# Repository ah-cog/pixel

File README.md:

Pixel
=====

Pixel is a modular, tangible interface for physical computing.

## Physical Design ##

TinkerCad
https://tinkercad.com/dashboard/projects/bFf1tuIbj8z-pixel

Autodesk 123D Design
http://123dapp.com/Project/Pixel/1861964

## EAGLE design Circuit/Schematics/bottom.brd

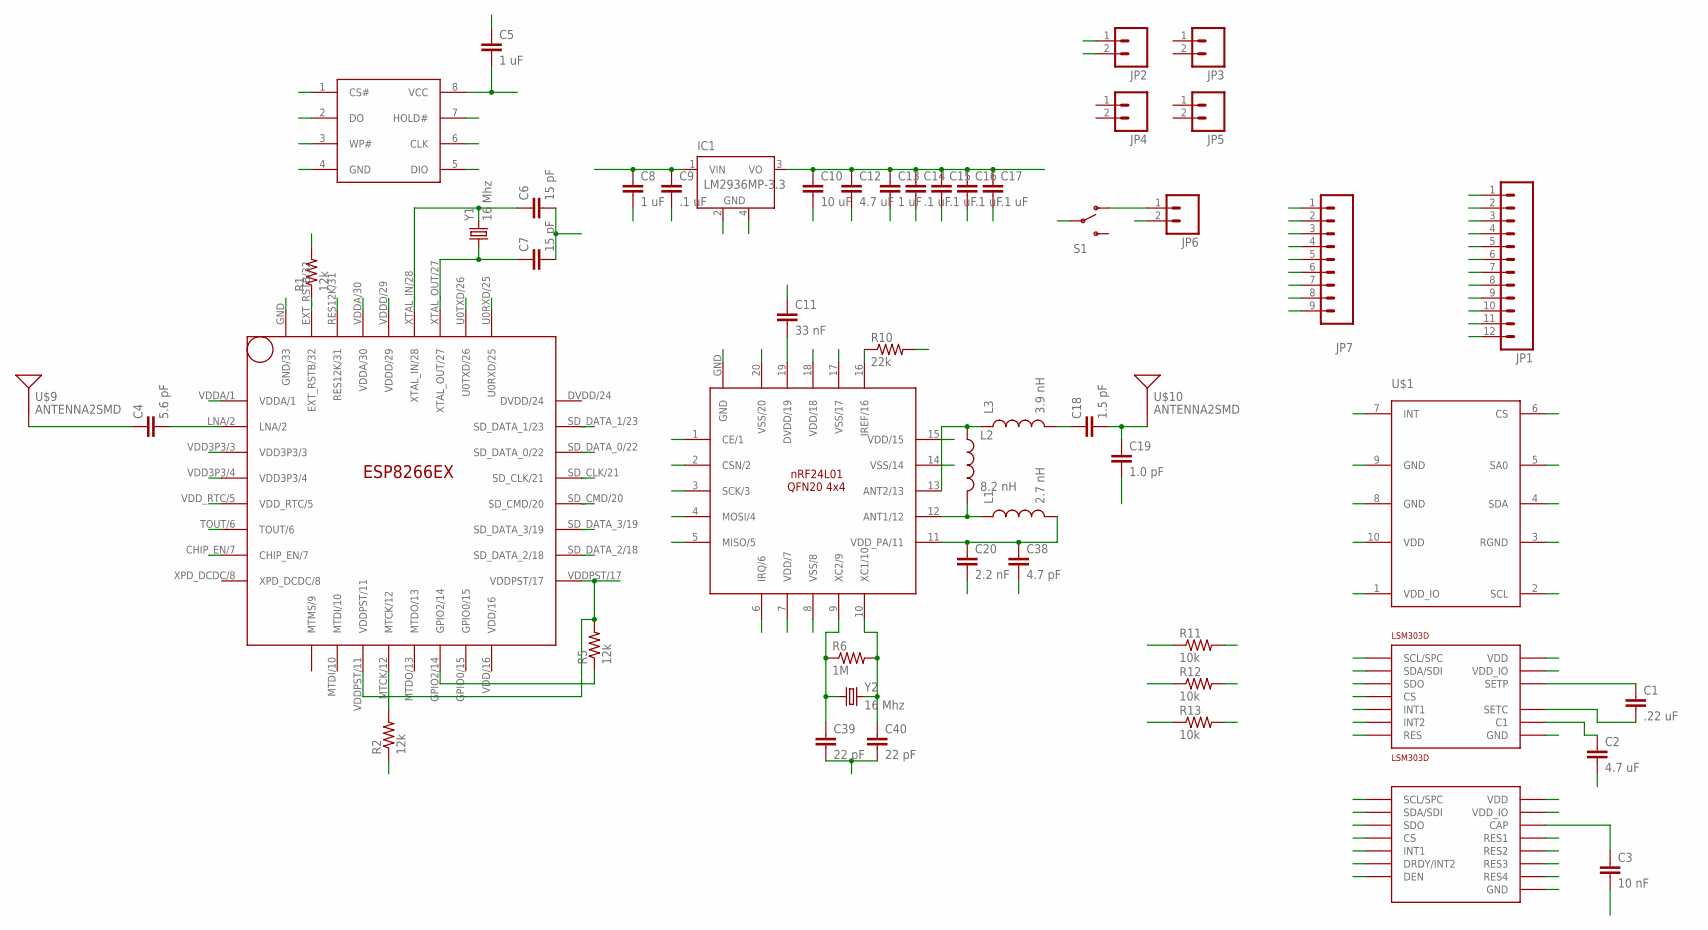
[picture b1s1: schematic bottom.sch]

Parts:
C1: .22 uF; 0603-CAP
C2, C12: 4.7 uF; 0603-CAP
C3: 10 nF; 0603-CAP
C4: 5.6 pF; 0603-CAP
C5, C8, C13: 1 uF; 0603-CAP
C6, C7: 15 pF; 0603-CAP
C9, C14, C15, C16, C17: .1 uF; 0603-CAP
C10: 10 uF; 0603-CAP
C11: 33 nF; 0603-CAP
C18: 1.5 pF; 0603-CAP
C19: 1.0 pF; 0603-CAP
C20: 2.2 nF; 0603-CAP
C38: 4.7 pF; 0603-CAP
C39, C40: 22 pF; 0603-CAP
IC1: LM2936MP-3.3; SOT223
JP1: M12PTH; 1X12
JP2, JP3, JP4, JP5, JP6: M02LOCK; 1X02_LOCK
JP7: M09; 1X09
L1: 2.7 nH; C0402
L2: 8.2 nH; C0402
L3: 3.9 nH; C0402
L3GD20H: L3GD20H; LGA16L
LSM303D: LSM303D; LGA16L
MESH: NRF24L01; QFN20(4X4)
R1, R2, R5: 12k; 0603-RES
R6: 1M; 0603-RES
R10: 22k; 0603-RES
R11, R12, R13: 10k; 0603-RES
S1: SWITCH-SPDT-SMD-A; SWITCH-SPST-SMD-A
U$1: LPS25H
U$9, U$10: ANTENNA2SMD; ANTENNA-CHIP2
WIFI: ESP8266EX; QFN32
WIFI_STORAGE: 25Q40; SOP8
Y1, Y2: 16 Mhz; CRYSTAL-SMD-5X3

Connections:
CE: JP7.3, MESH.1 (CE/1)
CSN: JP7.4, MESH.2 (CSN/2)
GND: C2.2, C3.2, C5.1, C6.2, C7.2, C8.2, C9.2, C10.2, C11.1, C12.2, C13.2, C14.2, C15.2, C16.2, C17.2, C19.2, C20.2, C38.2, C39.2, C40.2, IC1.2 (GND), IC1.4 (GND), JP1.1, JP1.2, JP1.3, JP1.4, JP1.5, JP1.6, JP2.2, JP6.2, L3GD20H.P$8 (DEN), L3GD20H.P$9 (RES1), L3GD20H.P$10 (RES2), L3GD20H.P$11 (RES3), L3GD20H.P$12 (GND), L3GD20H.P$13 (GND), LSM303D.P$5 (GND), LSM303D.P$10 (RES), LSM303D.P$12 (GND), LSM303D.P$13 (GND), LSM303D.P$16 (GND), MESH.8 (VSS/8), MESH.14 (VSS/14), MESH.17 (VSS/17), MESH.20 (VSS/20), R1.2, R2.1, R10.2, U$1.3 (RGND), U$1.8 (GND), U$1.9 (GND), WIFI.GND (GND/33), WIFI_STORAGE.4 (GND)
IQR: MESH.6 (IRQ/6)
MISO: JP7.6, MESH.5 (MISO/5)
MOSI: JP7.5, MESH.4 (MOSI/4)
unnamed: C4.1, U$9.FEED
unnamed: R5.1, WIFI.GPIO2/14
unnamed: R2.2, WIFI.MTCK/12
unnamed: L1.1, L2.2, MESH.12 (ANT1/12)
unnamed: C18.1, L3.2
unnamed: C18.2, C19.1, U$10.FEED
unnamed: C4.2, WIFI.LNA/2
unnamed: C39.1, MESH.9 (XC2/9), R6.1, Y2.1
unnamed: C40.1, MESH.10 (XC1/10), R6.2, Y2.3 (2)
unnamed: C20.1, C38.1, L1.2, MESH.11 (VDD_PA/11)
unnamed: L2.1, L3.1, MESH.13 (ANT2/13)
unnamed: MESH.16 (IREF/16), R10.1
unnamed: C11.2, MESH.19 (DVDD/19)
unnamed: C1.2, LSM303D.P$2 (SETC)
unnamed: C2.1, LSM303D.P$15 (C1)
unnamed: C3.1, L3GD20H.P$14 (CAP)
RST: R1.1, WIFI.EXT_RSTB/32
RTC: WIFI.VDD_RTC/5
RX_W: JP7.1, WIFI.U0TXD/26
SCK: JP7.7, MESH.3 (SCK/3)
SCL: JP7.9, L3GD20H.P$2 (SCL/SPC), LSM303D.P$4 (SCL/SPC), R12.2, U$1.2 (SCL)
SD-CLK: WIFI.SD_CLK/21, WIFI_STORAGE.6 (CLK)
SD-CMD: WIFI.SD_CMD/20, WIFI_STORAGE.1 (CS#)
SD-D0: WIFI.SD_DATA_0/22, WIFI_STORAGE.2 (DO)
SD-D1: WIFI.SD_DATA_1/23, WIFI_STORAGE.5 (DIO)
SD-D2: WIFI.SD_DATA_2/18, WIFI_STORAGE.7 (HOLD#)
SD-D3: WIFI.SD_DATA_3/19, WIFI_STORAGE.3 (WP#)
SDA: JP7.8, L3GD20H.P$3 (SDA/SDI), LSM303D.P$6 (SDA/SDI), R11.2, U$1.4 (SDA)
SDO: L3GD20H.P$4 (SDO), LSM303D.P$7 (SDO), R13.2, U$1.5 (SA0)
SETP: C1.1, LSM303D.P$3 (SETP)
TOUT: WIFI.TOUT/6
TX_W: JP7.2, WIFI.U0RXD/25
VIN: JP6.1, S1.1 (O)
VRAW: C8.1, C9.1, IC1.1 (VIN), S1.2
XTAL_IN: C6.1, WIFI.XTAL_IN/28, Y1.3 (2)
XTAL_OUT: C7.1, WIFI.XTAL_OUT/27, Y1.1

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
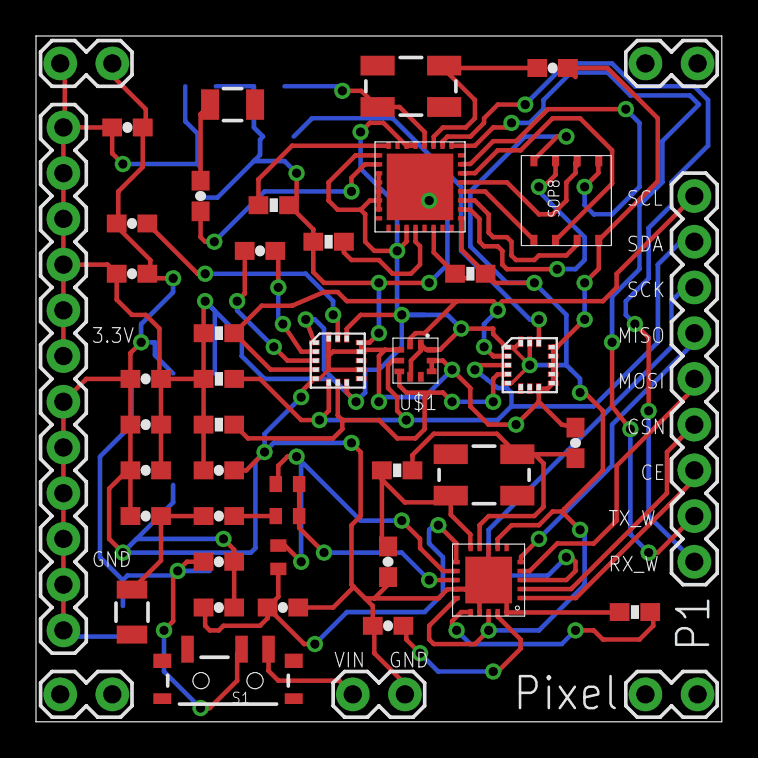
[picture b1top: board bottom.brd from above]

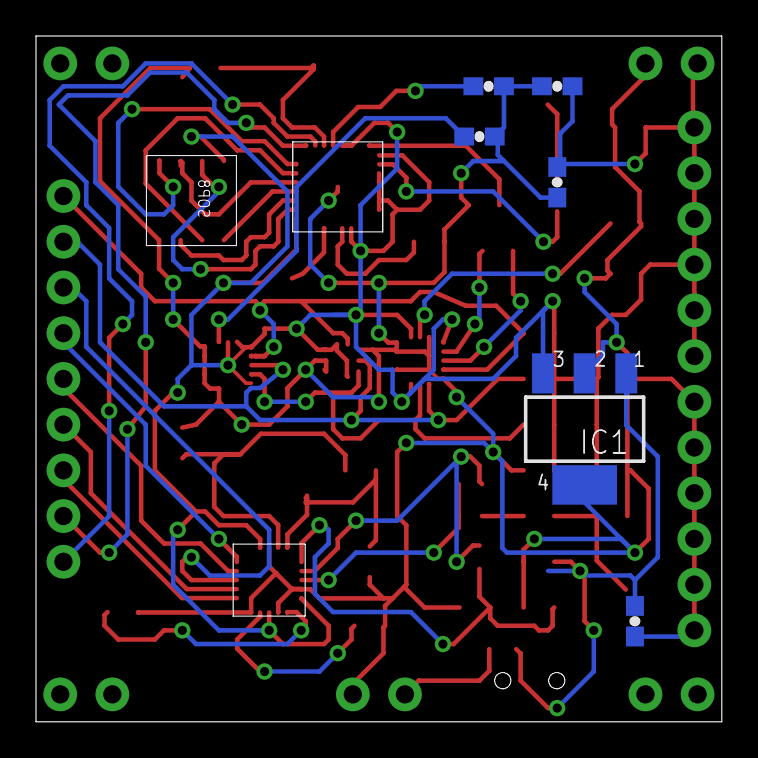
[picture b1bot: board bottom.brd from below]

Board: 2 copper layers, 38.1 x 38.1 mm, 53 parts (6 on the bottom side), 40 nets.

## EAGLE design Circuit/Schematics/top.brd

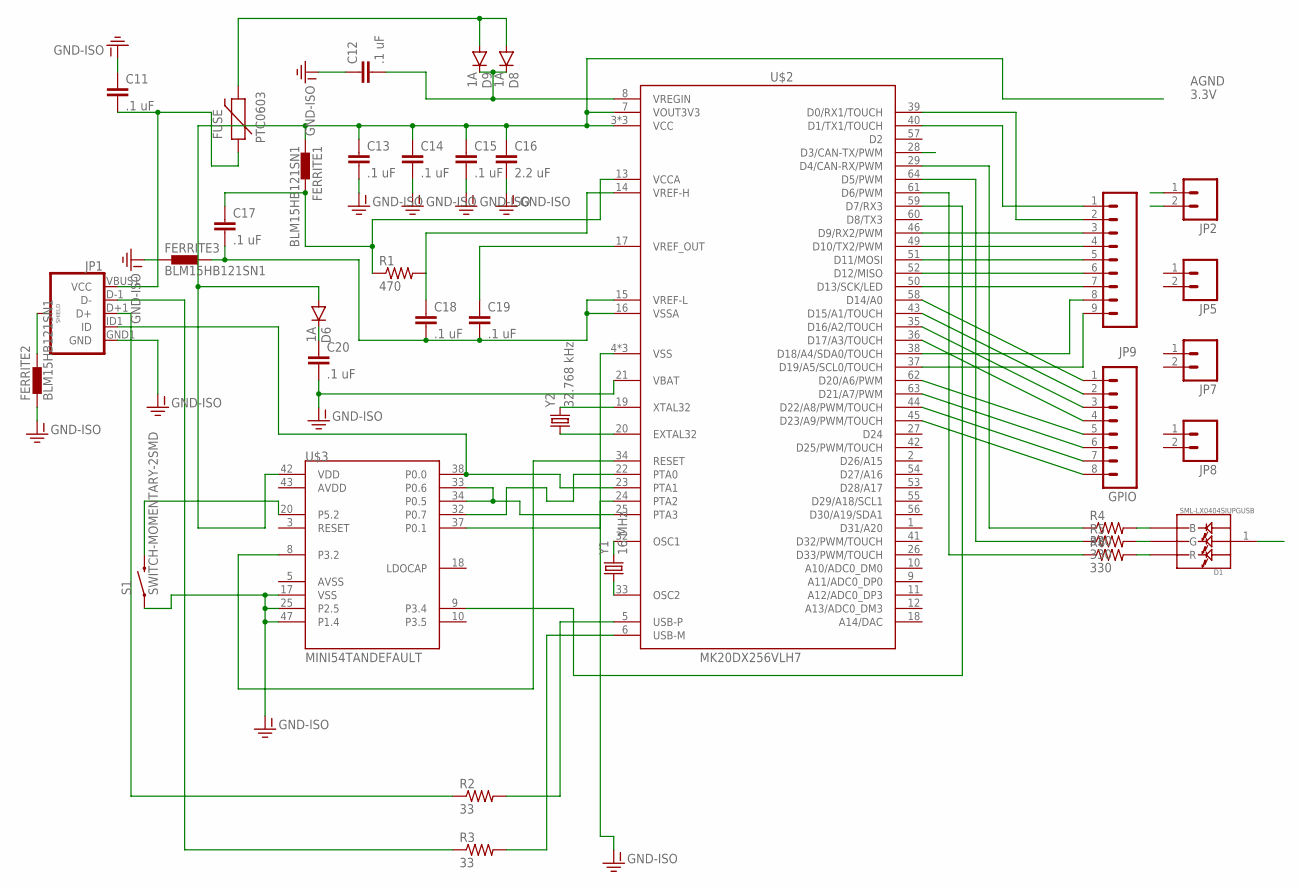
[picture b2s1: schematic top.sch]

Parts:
C11, C12, C13, C14, C15, C17, C18, C19, C20: .1 uF; 0603-CAP
C16: 2.2 uF; 0603-CAP
D1: SML-LX0404SIUPGUSB; 1MM_SQ_4PAD
D6, D8, D9: 1A; SOD-323
FERRITE1, FERRITE2, FERRITE3: BLM15HB121SN1; 0402
FUSE: PTC0603; 0603
GPIO: M08SILK_FEMALE_PTH; 1X08
JP1: USB_MICROB_PLUGCONN-11752; USB-B-MICRO-SMD_V03
JP2, JP5, JP7, JP8: M02LOCK; 1X02_LOCK
JP9: M09; 1X09
R1: 470; 0603-RES
R2, R3: 33; 0603-RES
R4, R5, R6: 330; 0603-RES
S1: SWITCH-MOMENTARY-2SMD; TACTILE-SWITCH-SMD
U$2: MK20DX256VLH7; QFP50P1200X1200X160-64N
U$3: MINI54TANDEFAULT; QFP50P900X900X160-48N
Y1: 16 MHz; CRYSTAL-SMD-5X3
Y2: 32.768 kHz; CRYSTAL-SMD-5X3

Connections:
3.3V: C13.1, C14.1, C15.1, C16.1, D1.1 (VDD), D6.A, FERRITE1.1, JP2.1, U$2.3 (VCC), U$2.7 (VOUT3V3), U$2.30 (VCC), U$2.48 (VCC), U$3.42 (VDD)
AGND: C17.2, C18.2, C19.2, FERRITE3.2, U$2.15 (VREF-L), U$2.16 (VSSA)
CE: JP9.3, U$2.46 (D9/RX2/PWM)
GND-ISO: C11.1, C12.1, C13.2, C14.2, C15.2, C16.2, C20.2, FERRITE2.1, FERRITE3.1, JP1.GND1 (GND), JP2.2, S1.1, U$2.4 (VSS), U$2.21 (VBAT), U$2.31 (VSS), U$2.47 (VSS), U$3.17 (VSS), U$3.25 (P2.5), U$3.47 (P1.4)
unnamed: C19.1, U$2.17 (VREF_OUT)
unnamed: C12.2, D8.C, D9.C, U$2.8 (VREGIN)
unnamed: C17.1, FERRITE1.2, R1.1, U$2.13 (VCCA)
unnamed: C18.1, R1.2
unnamed: FERRITE2.2, JP1.SHIELD1 (SHIELD), JP1.SHIELD2 (SHIELD), JP1.SHIELD3 (SHIELD)
unnamed: S1.3 (2), U$3.20 (P5.2)
unnamed: C20.1, D6.C
unnamed: JP1.D+1 (D+), R2.1
unnamed: U$2.34 (RESET), U$3.8 (P3.2)
unnamed: JP1.ID1 (ID), U$2.23 (PTA1), U$3.38 (P0.0)
unnamed: U$2.25 (PTA3), U$3.33 (P0.6), U$3.34 (P0.5)
unnamed: U$2.22 (PTA0), U$3.32 (P0.7)
unnamed: U$2.24 (PTA2), U$3.37 (P0.1)
unnamed: U$2.59 (D7/RX3), U$3.9 (P3.4)
unnamed: JP1.D-1 (D-), R3.1
unnamed: R2.2, U$2.5 (USB-P)
unnamed: R3.2, U$2.6 (USB-M)
unnamed: JP9.4, U$2.49 (D10/TX2/PWM)
unnamed: U$2.19 (XTAL32), Y2.3 (2)
unnamed: U$2.20 (EXTAL32), Y2.1
unnamed: U$2.32 (OSC1), Y1.3 (2)
unnamed: U$2.33 (OSC2), Y1.1
unnamed: JP9.5, U$2.51 (D11/MOSI)
unnamed: JP9.6, U$2.52 (D12/MISO)
unnamed: GPIO.1, U$2.58 (D14/A0)
unnamed: GPIO.2, U$2.43 (D15/A1/TOUCH)
unnamed: GPIO.3, U$2.35 (D16/A2/TOUCH)
unnamed: D1.3 (B), R4.2
unnamed: D1.4 (G), R5.2
unnamed: D1.2 (R), R6.2
unnamed: GPIO.4, U$2.36 (D17/A3/TOUCH)
unnamed: GPIO.5, U$2.62 (D20/A6/PWM)
unnamed: GPIO.6, U$2.63 (D21/A7/PWM)
unnamed: GPIO.7, U$2.44 (D22/A8/PWM/TOUCH)
unnamed: GPIO.8, U$2.45 (D23/A9/PWM/TOUCH)
unnamed: R5.1, U$2.64 (D5/PWM)
unnamed: R4.1, U$2.29 (D4/CAN-RX/PWM)
unnamed: C11.2, FUSE.1, JP1.VBUS1 (VCC)
unnamed: R6.1, U$2.61 (D6/PWM)
SCK: JP9.7, U$2.50 (D13/SCK/LED)
SCL_T: JP9.9, U$2.37 (D19/A5/SCL0/TOUCH)
SDA_T: JP9.8, U$2.38 (D18/A4/SDA0/TOUCH)
T_RX: JP9.2, U$2.39 (D0/RX1/TOUCH)
T_TX: JP9.1, U$2.40 (D1/TX1/TOUCH)
VIN: D8.A, D9.A, FUSE.2

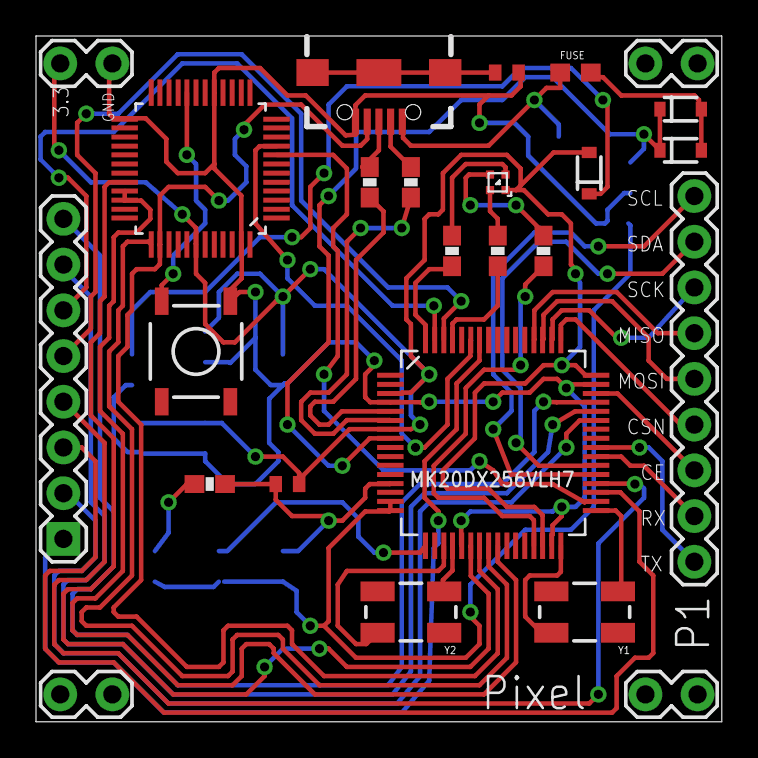
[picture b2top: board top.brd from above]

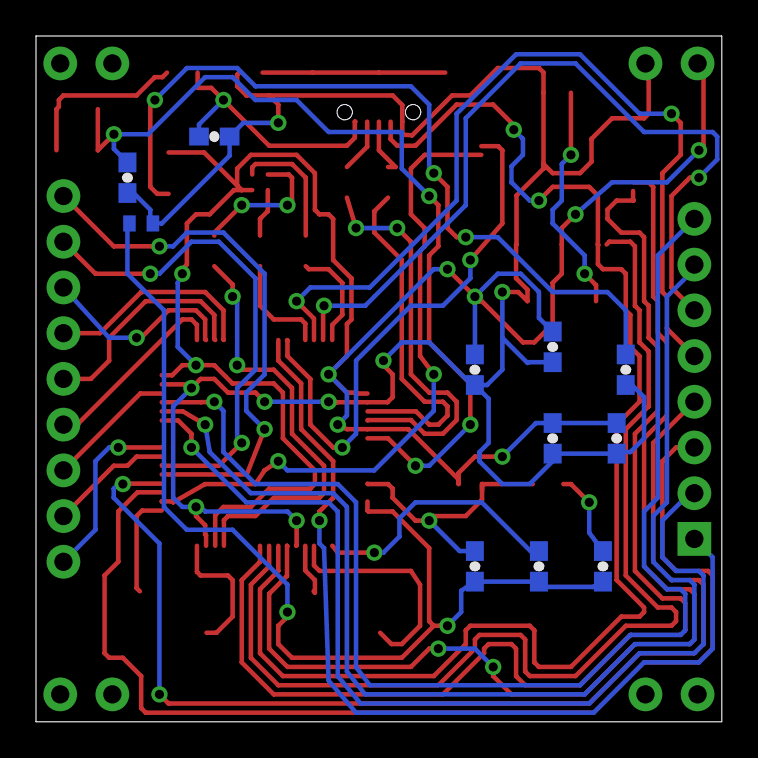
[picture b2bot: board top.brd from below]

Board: 2 copper layers, 38.1 x 38.1 mm, 36 parts (11 on the bottom side), 49 nets.

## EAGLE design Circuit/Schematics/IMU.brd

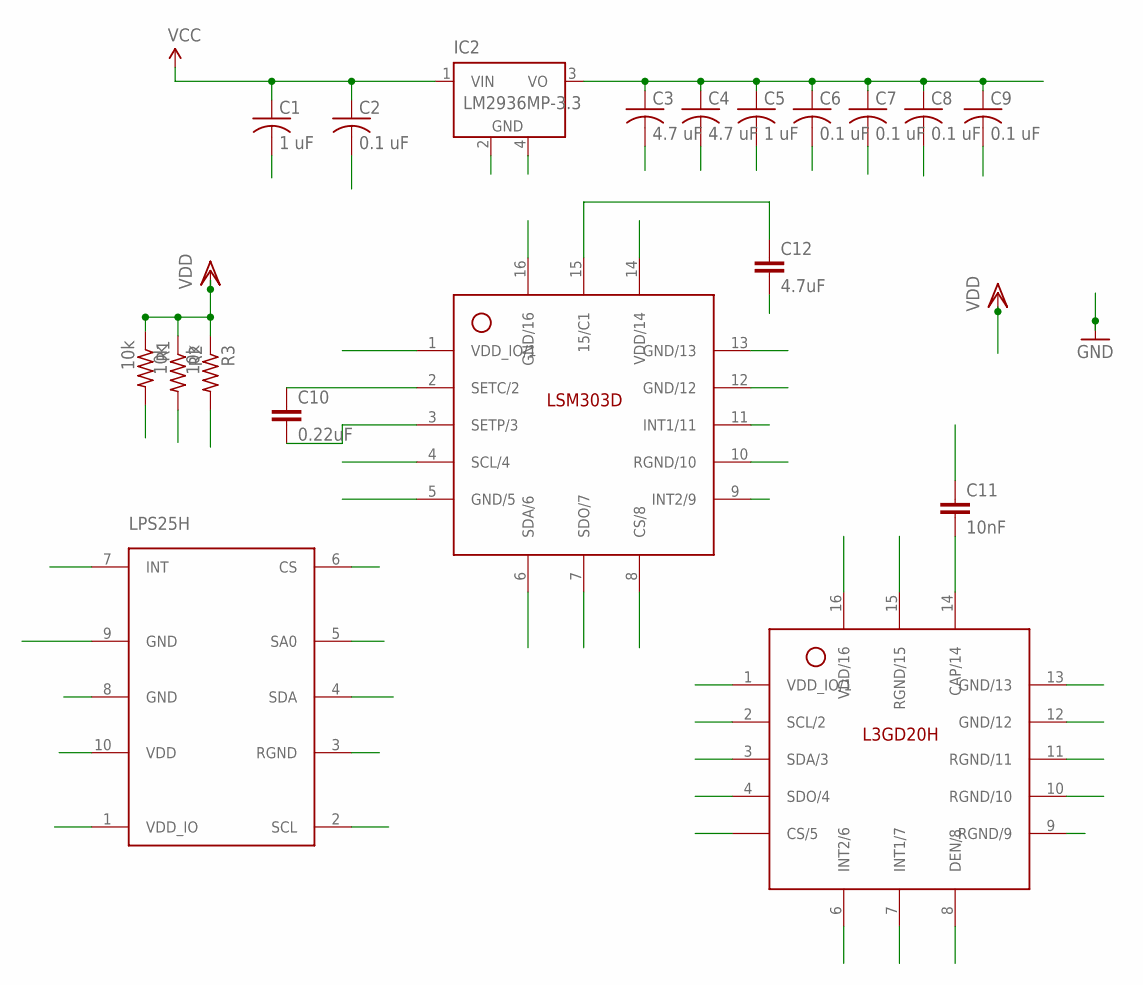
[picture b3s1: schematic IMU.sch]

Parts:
C1, C5: 1 uF; C0805
C2, C6, C7, C8, C9: 0.1 uF; C0805
C3, C4: 4.7 uF; C0805
C10: 0.22uF; 0603-CAP
C11: 10nF; 0603-CAP
C12: 4.7uF; 0603-CAP
IC2: LM2936MP-3.3; SOT223
LPS25H: LPS25H
R1, R2, R3: 10k; R0805
U$1: L3GD20H; LGA-16
U$2: LSM303D; LGA-16

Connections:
GND: C1.2, C2.2, C3.2, C4.2, C5.2, C6.2, C7.2, C8.2, C9.2, C11.1, C12.2, IC2.2 (GND), IC2.4 (GND), LPS25H.8 (GND), LPS25H.9 (GND), U$1.8 (DEN/8), U$1.9 (RGND/9), U$1.10 (RGND/10), U$1.11 (RGND/11), U$1.12 (GND/12), U$1.13 (GND/13), U$1.16 (VDD/16), U$2.5 (GND/5), U$2.10 (RGND/10), U$2.12 (GND/12), U$2.13 (GND/13), U$2.16 (GND/16)
unnamed: C10.1, U$2.2 (SETC/2)
unnamed: C10.2, U$2.3 (SETP/3)
unnamed: C12.1, U$2.15 (15/C1)
unnamed: C11.2, U$1.14 (CAP/14)
SCL: LPS25H.2 (SCL), R2.2, U$1.2 (SCL/2), U$2.4 (SCL/4)
SDA: LPS25H.4 (SDA), R1.2, U$1.3 (SDA/3), U$2.6 (SDA/6)
SDO: LPS25H.5 (SA0), R3.2, U$1.4 (SDO/4), U$2.7 (SDO/7)
VCC: C1.1, C2.1, IC2.1 (VIN)
VDD: C3.1, C4.1, C5.1, C6.1, C7.1, C8.1, C9.1, IC2.3 (VO), LPS25H.1 (VDD_IO), LPS25H.6 (CS), LPS25H.10 (VDD), R1.1, R2.1, R3.1, U$1.1 (VDD_IO/1), U$1.5 (CS/5), U$1.15 (RGND/15), U$2.1 (VDD_IO/1), U$2.8 (CS/8), U$2.14 (VDD/14)

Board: 2 copper layers, 19 parts (0 on the bottom side), 10 nets, no tracks yet.

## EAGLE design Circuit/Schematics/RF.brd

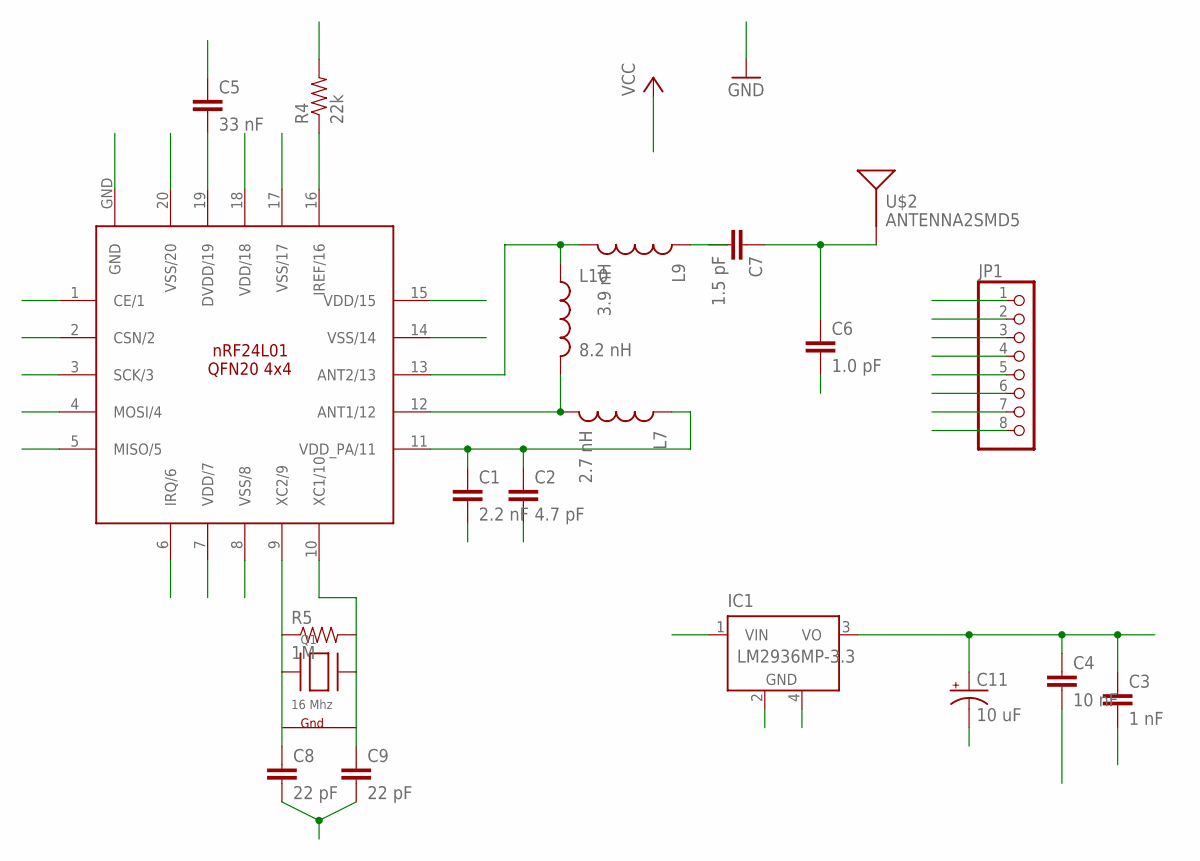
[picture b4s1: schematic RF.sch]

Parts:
C1: 2.2 nF; 0805
C2: 4.7 pF; 0805
C3: 1 nF; 0805
C4: 10 nF; 0805
C5: 33 nF; 0805
C6: 1.0 pF; 0805
C7: 1.5 pF; 0805
C8, C9: 22 pF; 0805
C11: 10 uF; EIA3216
IC1: LM2936MP-3.3; SOT223
JP1: PINHD-1X8BIG; 1X08-BIG
L7: 2.7 nH; C0402
L9: 3.9 nH; C0402
L10: 8.2 nH; C0402
Q1: 16 Mhz; NX3225
R4: 22k; 0805
R5: 1M; 0805
U$1: NRF24L01; QFN20(4X4)
U$2: ANTENNA2SMD5; ANTENNA-CHIP5

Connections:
ANT: C6.1, C7.1, U$2.FEED
CE: JP1.2, U$1.1 (CE/1)
CSN: JP1.3, U$1.2 (CSN/2)
G1: Q1.4 (G1)
G2: Q1.2 (G2)
GND: C1.2, C2.2, C3.2, C4.2, C5.1, C6.2, C8.2, C9.2, C11.C (-), IC1.2 (GND), IC1.4 (GND), JP1.8, R4.2, U$1.8 (VSS/8), U$1.14 (VSS/14), U$1.17 (VSS/17), U$1.20 (VSS/20), U$1.GND
IQR: JP1.7, U$1.6 (IRQ/6)
MISO: JP1.6, U$1.5 (MISO/5)
MOSI: JP1.5, U$1.4 (MOSI/4)
unnamed: C8.1, Q1.1 (X1), R5.1, U$1.9 (XC2/9)
unnamed: C9.1, Q1.3 (X2), R5.2, U$1.10 (XC1/10)
unnamed: C1.1, C2.1, L7.1, U$1.11 (VDD_PA/11)
unnamed: L7.2, L10.2, U$1.12 (ANT1/12)
unnamed: L9.2, L10.1, U$1.13 (ANT2/13)
unnamed: C7.2, L9.1
unnamed: R4.1, U$1.16 (IREF/16)
unnamed: C5.2, U$1.19 (DVDD/19)
SCK: JP1.4, U$1.3 (SCK/3)
VCC: IC1.1 (VIN)
VDD: C3.1, C4.1, C11.A (+), IC1.3 (VO), JP1.1, U$1.7 (VDD/7), U$1.15 (VDD/15), U$1.18 (VDD/18)

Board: 2 copper layers, 20 parts (0 on the bottom side), 17 nets, no tracks yet.

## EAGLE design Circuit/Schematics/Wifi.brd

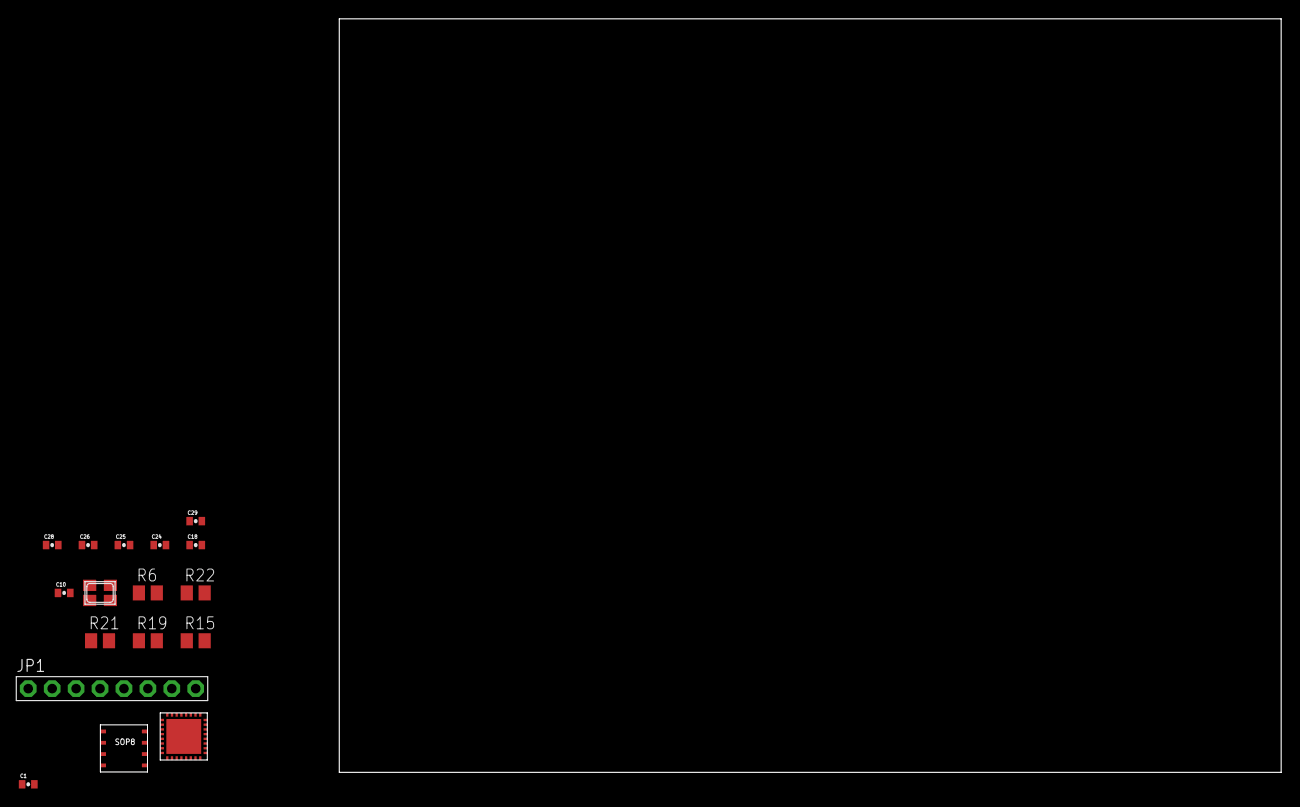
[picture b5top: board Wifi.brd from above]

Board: 2 copper layers, 125.3 x 79.9 mm, 17 parts (0 on the bottom side), 23 nets, no tracks yet.

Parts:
C1: 5.6 pF; 0402-CAP
C10, C24: 15 pF; 0402-CAP
C18: 1 uF; 0402-CAP
C25, C26, C29: 100 nF; 0402-CAP
C28: 10 uF; 0402-CAP
JP1: 1X08-BIG
Q1: NX3225
R6, R15, R19, R21: M0805
R22: 12k; M0805
U$1: ESP8266EX; QFN32
U$2: 25Q40; SOP8

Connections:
CHIP_EN: JP1.6, R21.2, U$1.CHIP_EN/7
CLK: U$1.SD_CLK/21, U$2.6
CS: U$1.SD_CMD/20, U$2.1
GND: C10.1, C18.1, C24.1, JP1.1, R15.2, R22.2, U$1.GND, U$2.4
unnamed: R22.1, U$1.RES12K/31
unnamed: C24.2, Q1.3, U$1.XTAL_IN/28
unnamed: C25.2, C26.2, C28.2, C29.2
unnamed: C10.2, Q1.1, U$1.XTAL_OUT/27
unnamed: R6.2, U$1.VDDPST/11, U$1.VDDPST/17
unnamed: R19.2, U$1.GPIO0/15
unnamed: R6.1, U$1.GPIO2/14
unnamed: R15.1, U$1.MTDO/13
unnamed: C1.1, U$1.LNA/2
RST: JP1.5, U$1.EXT_RSTB/32
RTC: JP1.8, U$1.VDD_RTC/5
RXD: JP1.3, U$1.U0RXD/25
SD0: U$1.SD_DATA_0/22, U$2.2
SD1: U$1.SD_DATA_1/23, U$2.5
SD2: U$1.SD_DATA_2/18, U$2.7
SD3: U$1.SD_DATA_3/19, U$2.3
TOUT: JP1.7, U$1.TOUT/6
TXD: JP1.4, U$1.U0TXD/26
VCC: C18.2, C25.1, C26.1, C28.1, C29.1, JP1.2, R19.1, R21.1, U$1.VDD3P3/3, U$1.VDD3P3/4, U$1.VDDA/1, U$1.VDDA/30, U$1.VDDD/29, U$2.8

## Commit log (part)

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2013-07-23 Initial commit.
2013-07-23 Added basic iterator to Arduino module code and Processing visualizer.
2013-10-05 HackMIT, Day 1 (Saturday). Got basic RadioBlock communication working between two Arduinos and RadioBlocks.
    Using Arduino Unos, each set up with a RadioBlock. The Arduino Uno with
    the RadioBlock with orange sticker labeled "0" is set with the address
    0x1000 (using the RadioBlockSerialInterface::setAddress() function).
    The other Arduino, labeled "1" is set with address 0x1001.
2013-10-05 HackMIT, Day 1 (Saturday). Code successfully communicates state of Switch 1 (SWT-GND1) on 2x2 button module.
2013-10-06 HackMIT, Day 1 (Saturday). Added initial button module LED control and I/O code.
2013-10-06 HackMIT, Day 2 (Sunday). Set sound for each row.
2013-10-06 HackMIT, Day 2 (Sunday). Added function to get button input and set button state.
2013-10-06 HackMIT, Day 2 (Sunday). Implemented column-by-column baseline iterator. Updated toggle behavior, particularly how lights are enabled.
2013-10-06 HackMIT, Day 2 (Sunday). Implemented simple sound playback on column activation.
2013-10-06 HackMIT, Day 2 (Sunday). Added basic state synchronization.
2013-10-12 HackRU, Day 1 (Saturday). Initial code. Basically same form HackMIT, but primed to change a lot in the next 20 hours.
2013-10-13 HackRU, Day 2 (Sunday). Added relay and accelerometer template sketches.
2013-10-13 HackRU, Day 2 (Sunday). Integrated accelerometer code into main node sketch.
2013-10-13 HackRU, Day 2 (Sunday). Added basic RadioBlocks code (untest).
2013-10-13 HackRU, Day 2 (Sunday). RadioBlocks verified to work. Next up, communicate meaningful information bi-directionally.
2013-10-13 HackRU, Day 2 (Sunday). Near-final code. Right now, nodes communicate, but don't affect each other.
2013-10-13 HackRU, Day 2 (Sunday). Final (?) demo code.
2013-11-03 Moved ModuleV1 and HUD code made while residing at the Tinkering Studio at The Exploratorium into a folder named Tinkering Studio.
2013-11-03 Added Arduino code for MinIMU-10 IMU for orientation sensing.
2013-11-03 (Once again…) Corrected naming problem in previous commit.
2013-11-04 Added AltIMU-10 support STL file.
2013-11-04 Fixed bug in Gesture Visualizer Deux. Added physical prototypes CAD files.
2013-11-11 Added CADf files for TinyDuino stack support.
2013-11-11 Updated TinyDuino stack support CAD file.
2013-11-11 Updated WiFi module support CAD file.
2013-11-11 Updated CAD file for TinyDuino Stack Support.
2013-11-11 Updated TinyDuino support CAD file.
2013-11-11 Cleaned up CC3000 web server code.
2013-11-12 Updated RadioBlocks and TinyDuino CAD files.
2013-11-22 Added new sketch that seems to integrate SD card reading and the WiFi module successfully. It's rather huge, though :-(.
2013-11-26 Added code templates. Added initial IMU data for creating gesture recognition heuristics.
2013-12-01 Added RadioBlocks example code.
2013-12-01 Added RadioBlocks Transmitter Demo for Arduino.
2013-12-02 Updated firmware with hard-coded (hack) code get device address and construct a list of neighbor addresses.
2013-12-02 Updated firmware. Added basic light control.
2013-12-15 Cleaned up firmware code.
2013-12-15 Updated firmware. Refactored firmware code.
2013-12-16 Updated firmware. Refactored, cleaned up.
2013-12-16 Updated firmware. Performs "ping pong".
2013-12-18 Updated firmware.
2013-12-24 Updated firmware. Added basic random pseudo-random number generator.
2013-12-26 Added data and data logger.
2013-12-26 Updated Visualizer. Added accelerometer and gyroscope data. Added basic plots.
2013-12-27 Created Gesture Data Plotter, a tool for helping construct gestural models from data.
2013-12-28 Added basic web-based creative interface.
2013-12-29 Added Looper. Replaced "Web Interface" with "Looper".
2013-12-29 Cleaned up Looper code.
2013-12-29 Updated Looper. Fixed big from last commit.
2014-01-01 Updated Looper. Added method to return event loop event seqeuence.
2014-01-01 Updated Looper. Added basic script renaming functionality.
2014-01-13 Update Gesture Data Plotter.
2014-01-31 (Work in progress.) Updated Looper with skeleton for dynamically adding multiple devices.
2014-02-02 Implemented basic multi-device interface. Time to clean up.
2014-02-02 Cleaned up.
2014-02-03 Cleanup and tweaks.
2014-02-03 Added "going" state variable to each event loop and ability to start and stop.
2014-02-03 Added Firepad.
2014-02-08 Updated Plotter.
2014-02-08 Updated Gesture Plotter. Got classification working pretty well for most gestures, almost always.
2014-02-08 Updated Gesture Plotter. Real-time gesture recognition demo. Hints that approach is okay, but needs tweaking.
2014-02-09 Renamed "Gesture Data Plotter" to "Gesture Plotter".
2014-02-09 Renamed "Gesture Visualizer Deux" to "Gesture Visualizer".
2014-02-09 Temporarily renamed "looper" to "Looper Behavior Sequencer".
2014-02-09 Updated Looper. Added basic behavior palette.
2014-02-09 Updated Looper. Added labels to behavior events.
2014-02-09 Updated Looper. Added behavior scripts to events in the event loop. The events execute the scripts to perform the behavior.
2014-02-09 Updated Looper. Added JavaScript code formatter.
2014-02-09 Updated Looper. Fixed behavior script ordering bug.
2014-02-15 Updated Gesture Visualizer and Looper.
2014-02-16 Updated Gesture Plotter. Cleaned up code.
2014-02-16 Updated Gesture Plotter and Data Transducer. Coded generator for Arduino gesture signatures.
2014-02-16 Updated IMU Data Transducer. Integrated gesture recognition code into Arduino code.
2014-02-24 Many updates and cleanup changes.
2014-03-04 Updated firmware. Added gesture sustain duration (how long the gesture is active, at minimum).
2014-03-04 Updated Gesture Plotter. Added gesture signature boundary visualization.
2014-03-05 Updated Gesture Plotter. Fixed a few bugs. Demoable.
2014-03-25 Updated Firmware. Moved gesture recognition code to separate header file.
2014-03-25 Renamed Gesture Plotter to Gesture Builder.
2014-03-26 Updated Gesture Builder. Fixed gesture matching window bug.
2014-03-27 Updated Looper Firmware.
2014-03-27 Updated Firmware. Demoable. Tested communication to be functional.
2014-03-29 Updated Firmware. Moved LED control code to Light.h.
2014-03-29 Updated Firmware. Moved gesture recognition code to Gesture.h.
    Gesture.h shouldn’t be confused with Gestures.h. Gestures.h contains
    only gesture models, generated by the Gesture Builder tool and doesn’t
    currently include functions for gesture recognition, too.
2014-03-29 Updated Firmware. Added RGB LED color gradual crossfade algorithm.
2014-03-29 Updated Firmware. Added incoming mesh message queue.
2014-03-30 Updated Firmware. Added function to return a Message structure for incoming messages (with source and message).
2014-03-30 Updated Firmware and Gesture Builder.
    Added module color, some sequencing logic and more to Firmware. Gesture
    Builder exporting tool for Gestures.h updated.
2014-03-30 Updated Gesture Builder. Added basic live classifier accuracy validation.
2014-03-30 Updated Gesture Builder. Added real-time, interactive gesture building.
2014-03-31 Cleaned up. Removed IMU Data Logger, Pixel Firmware Rendition 1, and PixelPingPong.
2014-03-31 Moved Gesture Visualizer and Pixel Firmware Gesture Classification to Historic folder.
2014-03-31 Renamed Physical Prototypes to Physical Design.
2014-03-31 Updated README.
2014-03-31 Updated Firmware. Added data structure and support functions for next and previous modules.
2014-03-31 Updated Firmware. Implemented basic linking.
2014-04-02 Updated Firmware. Refactored orientation sensing code.
2014-04-02 Updated Firmware. Cleanup.
2014-04-02 Updated Firmware. Refactored firmware project. Cleanup.
2014-04-02 Updated Firmware. Split the crossfading function so it can be called iteratively (or recursively).
2014-04-05 Updated Looper. Added live interactive play.
2014-04-05 Updated Looper. Set up basic code deployment framework.
2014-04-10 Updated Gesture Builder and Firmware.
2014-04-16 Updated Firmware. Added sequencing code.
2014-04-20 Added example for I2C communication between Teensy.
2014-04-20 Added bidirectional I2C master-slave communication.
2014-05-22 Tested working device-device comm. with web server.
2014-05-22 Roughly prototyped end-to-end process of serving a page with buttons, clicking one to generate an HTTP request, parsing that, then relaying it to a second Teensy via SPI.
2014-05-23 Added "erase" behavior.
2014-05-24 Refactored Looper web server code.
2014-06-02 Integrated I2C master code (for master-slave communication) into Pixel Firmware.
2014-06-03 Refactored firmware code.
2014-06-03 Added "delay" instruction to firmware.
2014-06-03 Added capacitative touch input to firmware.
2014-06-06 Integrated Looper browser interface into firmware. Doesn't yet work, though. Removed Firepad, Firebase, Ace, Beautify. Cleanup.
2014-06-06 Added commands for making "Blink" example to Looper.
2014-06-11 Updated module design files.
2014-06-17 Updated firmware with inklings of virtual Pixels.
2014-06-18 Updated remote control code (it works).
2014-06-19 Updated Gesture Builder. Updated gesture models, linking, etc.
2014-07-02 Added light behavior queue. Updated looper and other tweaks.
2014-07-21 Added gyroscope data to Gesture Builder.
2014-07-21 Refactored up Gesture Builder.
2014-07-21 Added "mode" indicator to Gesture Builder.
2014-07-27 Removed Gesture Builder (moved to physicalcomputer/gesture-builder).
2014-07-27 Moved firmware to "Firmware" folder.
2014-07-27 Updated README.md.
2014-07-27 Renamed "Physical Design" to "Module".
2014-08-03 Updated firmware. Added "read pin" request handler.
2014-08-04 Updated firmware. Implemented behavior removal.
2014-08-08 Updated firmware. Updated Device code.
2014-08-17 Updated Firmware Slave. Added dynamic memory management.
2014-08-24 Updated Firmware, mostly Looper firmware.
2014-08-26 Renamed "Pixel Firmware Slave" to "Looper Firmware".
    Looper is the behavior engine (computer) for Pixel.
2014-08-26 Renamed .ino for Looper Firmware.
2014-08-31 Updated Looper and Pixel Firmware.
2014-08-31 Updated Looper Firmware. Updated Performer. Added Delay.
2014-09-01 Update Pixel and Looper Firmware. Added parts of the Looper engine to Pixel.
2014-09-02 Updated Looper Firmware. Renamed Propagation to Transformation.
2014-09-04 Updated Looper/Pixel Firmware. Fixed bug in I2C communication code.
2014-09-09 Updated Firmware. Added delay functionality.
2014-09-15 Updated Pixel Firmware. Refactored.
2014-09-16 Updated Firmware. Updated gestural interaction between modules.
2014-09-25 Updated Firmware. Massively.
2014-09-28 Updated Pixel Firmware. Added mesh communications for RF266.
2014-10-11 Updated Firmware. Replaced I2C with Serial communication for board-board communication. Added Module Prototype 4 designs.
2014-11-13 Updated Firmware. Added console.
2014-11-23 Updated Firmware. Implemented general text communication.
2014-11-26 Updated Firmware. Updated textual language.
2014-11-26 Updated Firmware. Added simple simulated memory.
2014-11-29 Updated Firmware. Updated color interpreter.
2014-12-03 Updated Firmware. Cleanup, tweaks, and experiments.
2015-02-18 Updated Looper Firmware. Implemented discovery.
2015-03-08 Updated Firmware. Added support to change memory values in stored (key, value) memories.
2015-03-08 Updated Firmware. Renamed "language behavior" to "immediate" behavior and added "...now" modifier to make the performer execute a behavior before continuing onto the next behavior as usual.
2015-03-21 Cleaned up repository. Added ShopBot Desktop PCB milling files.
2015-03-21 Cleanup. Removed logs and temporary files related to PCB fabrication on ShopBot Desktop.
2015-03-22 Removed old firmware versions.
2015-03-22 Added a components list named Components.md.
2015-03-22 Added schematics for ESP8266, nRF24L01+, and Pololu IMU 9DOF v3.
2015-03-26 Added Connections.md and updated Components.md. Added dottiest for Pololu IMU.
2015-04-17 IMU completed
2015-06-02 Wifi and mesh board crappy designed
2015-06-06 Teensy board designed, redesigning system components board and making hardware components consistent
2015-06-06 System components board almost done. Final tweaking

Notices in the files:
parts and their libraries:
SparkFun-Capacitors: Licensing: Creative Commons ShareAlike 4.0 International - https://creativecommons.org/licenses/by-sa/4.0
SparkFun-Aesthetics: Licensing: CC v3.0 Share-Alike You are welcome to use this library for commercial purposes.
